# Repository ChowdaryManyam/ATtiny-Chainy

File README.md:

# ATtiny-Chainy 🔑

## Overview
ATtiny-Chainy is an innovative, compact circular development board that reimagines the potential of microcontroller design for makers and electronics enthusiasts. Built around the powerful Microchip ATtiny85 microcontroller, this board transforms the concept of a traditional development platform into a versatile, portable, and user-friendly solution. The ATtiny85 is a high-performance, low-power 8-bit AVR RISC-based microcontroller that packs significant capabilities into a tiny package. With 8KB of in-system programmable flash memory, 512 bytes of EEPROM, and 512 bytes of internal SRAM, this microcontroller offers robust functionality for a wide range of embedded projects. Its ability to operate at clock frequencies up to 20 MHz and support for various communication interfaces makes it an ideal choice for small-scale, creative electronics endeavors.

## Key Features 🌟
- **Circular PCB Design**: Unique form factor that's both functional and eye-catching
- **Keychain Compatible**: Integrated punch hole for easy carrying
- **M2 Mounting Option**: Secure attachment to platforms using a standard M2 screw
- **Single-Layer PCB**: Easy to manufacture at home using chemical etching or CNC routing
- **Minimalist Component Design**: Perfect for hobbyists and makers

## Technical Specifications 🛠️
- **Microcontroller**: ATtiny85
- **Programming Interface**: Micro USB port for direct PC programming via Arduino IDE
- **Power Options**: 
  - USB-powered
  - External supply through Vin
  - 5V supply pins
- **Operating Voltage Range**: 1.7V to 5.5V
- **Experimental Power Option**: Direct LiPo battery connection to 5V pins (use with caution)
- **Form Factor**: Circular PCB
- **Mounting Options**: 
  - Keychain attachment
  - M2 screw mounting
- **Layer Count**: Single Layer
- **Compatibility**: Arduino IDE programmable

## OSHWA Certification
ATtiny-Chainy has been officially certified as open source hardware by the Open Source Hardware Association (**OSHWA**). 

- **Certification UID**: DE000151
- **Certification Directory Listing**: [View Listing](https://certification.oshwa.org/list.html)
- **Project Directory**: [Direct Link](https://certification.oshwa.org/de000151.html)

As an OSHWA-certified project, ATtiny-Chainy adheres to the open-source hardware definition, ensuring transparency, collaboration, and accessibility for the maker community. The certification mark can be used alongside this project in compliance with OSHWA guidelines.

## Getting Started 
Makers can quickly get started with ATtiny-Chainy by cloning the repository, reviewing the schematic, and manufacturing the PCB using their preferred method. The board's design emphasizes simplicity and accessibility, allowing both novice and experienced electronics enthusiasts to bring their projects to life with minimal barriers to entry.

## License 📄
ATtiny-Chainy is released under the Creative Commons Attribution-ShareAlike 4.0 International (CC BY-SA 4.0) license. This means the project is freely available for sharing, adaptation, modification, and redistribution, with the requirement of providing appropriate credit to the original creator. The open-source nature of this project encourages collaboration, learning, and innovation within the maker community.
- ATtiny-Chainy © 2024 by Chowdary Manyam (Schrodinger Guru) is licensed under CC BY-SA 4.0 

## Inspiration 
Inspired by DigiStump's DigiSpark, ATtiny-Chainy takes the concept of a compact development board and elevates it with a unique circular design, enhanced portability, and maker-friendly features. It represents a fusion of practical design and creative engineering.

## Disclaimer 
This is a community project. Always follow proper electronics safety guidelines when working with microcontrollers and PCBs. The experimental power options, such as direct LiPo battery connection, should be approached with caution and a proper understanding of electrical characteristics.

---

**Happy Making!**

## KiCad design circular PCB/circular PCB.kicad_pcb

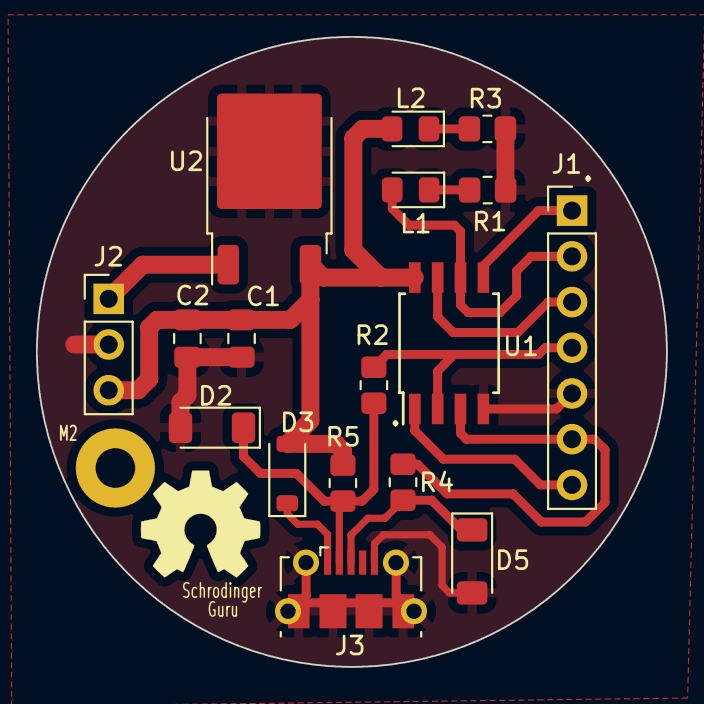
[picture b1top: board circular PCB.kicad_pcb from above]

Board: 2 copper layers, 35.0 x 35.0 mm, 18 parts (0 on the bottom side), 14 nets.

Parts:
C1: 4.7uF; C_0805_2012Metric_Pad1.18x1.45mm_HandSolder
C2: 0.1uF; C_0805_2012Metric_Pad1.18x1.45mm_HandSolder
D2, D5: BZV55B3V6; D_MiniMELF
D3: MBR0520LT; D_SOD-123
J1: Conn_01x07_Socket; PinHeader_1x07_P2.54mm_Vertical
J2: Conn_01x03_Pin; PinHeader_1x03_P2.54mm_Vertical
J3: USB3_B_Micro; USB_Micro-B_Molex-105017-0001
L1, L2: LED; LED_0805_2012Metric_Pad1.15x1.40mm_HandSolder
M2: MountingHole_2.2mm_M2_Pad
R1, R3: 10k; R_0805_2012Metric_Pad1.20x1.40mm_HandSolder
R2, R4: 68R; R_0805_2012Metric_Pad1.20x1.40mm_HandSolder
R5: 1.5k; R_0805_2012Metric_Pad1.20x1.40mm_HandSolder
U1: ATtiny85-20S; SOIC-8W_5.3x5.3mm_P1.27mm
U2: L7805; TO-252-2

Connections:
+5V: C1.1, C2.1, D3.2 (A), J2.3, L2.2 (A), R5.2, U1.8 (VCC), U2.3 (OUT)
GND1: C1.2, C2.2, D2.2 (A), D5.2 (A), J1.5, J2.2, J3.5 (GND), R1.2, R3.2, U1.4 (GND), U2.2 (GND)
unnamed: J1.2, L1.2 (A), U1.6 (PB1)
unnamed: L1.1 (K), R1.1
unnamed: D2.1 (K), J3.2 (D-), R2.1, R5.1
unnamed: D3.1 (K), J3.1 (VBUS)
unnamed: L2.1 (K), R3.1
unnamed: D5.1 (K), J3.3 (D+), R4.1
unnamed: J1.1, U1.5 (AREF/PB0)
unnamed: J1.3, U1.7 (PB2)
unnamed: J1.4, R2.2, U1.2 (XTAL1/PB3)
unnamed: J1.6, R4.2, U1.3 (XTAL2/PB4)
unnamed: J1.7, U1.1 (~RESET/PB5)
unnamed: J2.1, U2.1 (IN)

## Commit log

2024-12-07 Licence-Update README.md
    Added the CC license description to the original README script
2024-12-13 OSHWA update README.md
